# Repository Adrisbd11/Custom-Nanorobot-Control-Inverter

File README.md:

# Scalable Power Inverter for Precision Magnetic Field Control
This project is motivated by the growing interest in magnetic actuation systems for controlling microrobots and nanorobots in biomedical applications. These devices can be guided remotely using externally generated magnetic fields, enabling precise navigation inside the human body without the need for invasive procedures. Potential applications include targeted drug delivery, minimally invasive surgery, and the removal of blockages in blood vessels.

To achieve accurate control of these robots, it is necessary to generate well-defined and time-varying magnetic fields. This is typically done using current-driven coils, where the magnetic field is directly related to the current flowing through the windings. As a result, precise current control becomes a critical requirement for reliable and repeatable operation.

In this context, the project focuses on the design of a power inverter capable of driving a high-inductance coil with controlled current. The system is designed to operate with a coil of approximately 300 mH, supplying currents in the range of 20–30 A, and powered from a 560 V DC bus. These specifications impose significant challenges in terms of voltage handling, current regulation, and transient management in an inductive load.

This implementation represents a first functional prototype intended for laboratory validation. However, the design is conceived with scalability in mind, allowing extension toward significantly larger and more complex systems requiring higher power levels, multiple coils, and more advanced magnetic field control.  The system is designed to operate with a coil of approximately 100 mH, supplying currents in the range of 1–15 A, and powered from a 60-100 V DC bus.

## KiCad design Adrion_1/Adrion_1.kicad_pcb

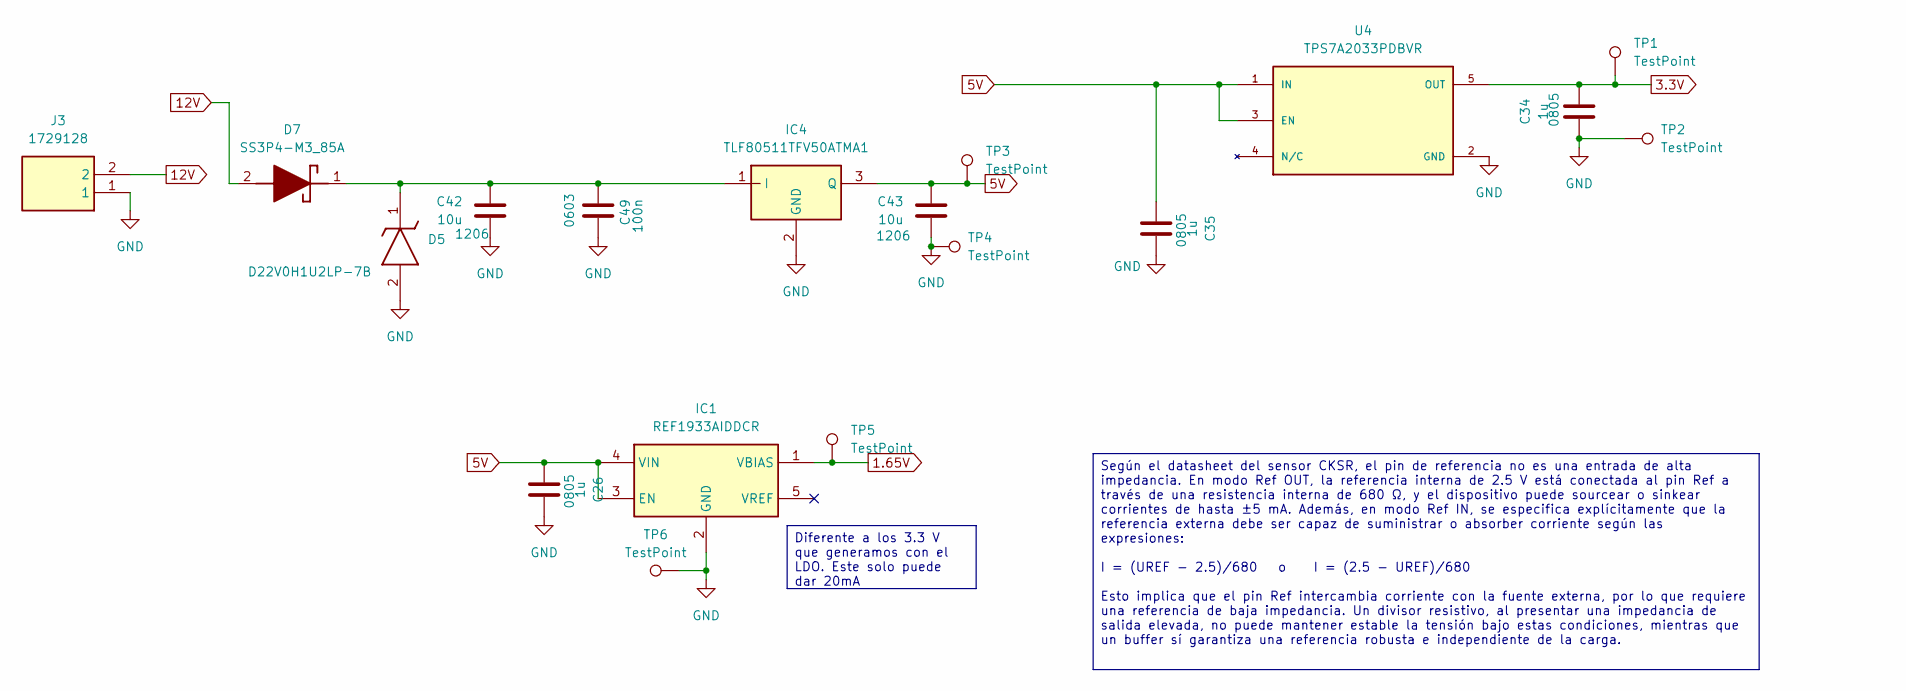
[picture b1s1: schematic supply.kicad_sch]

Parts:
C26, C34, C35: 1u; C_0805_2012Metric
C42, C43: 10u; C_1206_3216Metric
C49: 100n; C_0603_1608Metric
D5: D22V0H1U2LP-7B; D22V0H1U2LP7B; Manufacturer_Part_Number D22V0H1U2LP-7B
D7: SS3P4-M3_85A; SS3P4M385A; Manufacturer_Part_Number SS3P4-M3/85A; Mouser Part Number 625-SS3P4-M3/85A
IC1: REF1933AIDDCR; SOT95P280X110-5N; Manufacturer_Part_Number REF1933AIDDCR; Mouser Part Number 595-REF1933AIDDCR
IC4: TLF80511TFV50ATMA1; IDD09E60; Manufacturer_Part_Number TLF80511TFV50ATMA1; Mouser Part Number 726-TLF80511TFV50ATM
J3: 1729128; Manufacturer_Part_Number 1729128; Mouser Part Number 651-1729128
TP1, TP2, TP3, TP4, TP5, TP6: TestPoint; TestPoint_Pad_D1.0mm
U4: TPS7A2033PDBVR; SOT95P280X145-5N; PARTREV H

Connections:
1.65V: IC1.1 (VBIAS), TP5.1; also elsewhere on the board
3.3V: C34.2, TP1.1, U4.5 (OUT); also elsewhere on the board
5V: C26.1, C35.1, C43.1, IC1.3 (EN), IC1.4 (VIN), IC4.3 (Q), TP3.1, U4.1 (IN), U4.3 (EN); also elsewhere on the board
12V: D7.2 (A), J3.2; also elsewhere on the board
GND: C26.2, C34.1, C35.2, C42.2, C43.2, C49.1, D5.2 (A), IC1.2 (GND), IC4.2 (GND), J3.1, TP2.1, TP4.1, TP6.1, U4.2 (GND); also elsewhere on the board
unnamed: C42.1, C49.2, D5.1 (K), D7.1 (K), IC4.1 (I)

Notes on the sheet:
Diferente a los 3.3 V que generamos con el LDO. Este solo puede dar 20mA
Según el datasheet del sensor CKSR, el pin de referencia no es una entrada de alta impedancia. En modo Ref OUT, la referencia interna de 2.5 V está conectada al pin Ref a través de una resistencia interna de 680 Ω, y el dispositivo puede sourcear o sinkear corrientes de hasta ±5 mA. Además, en modo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

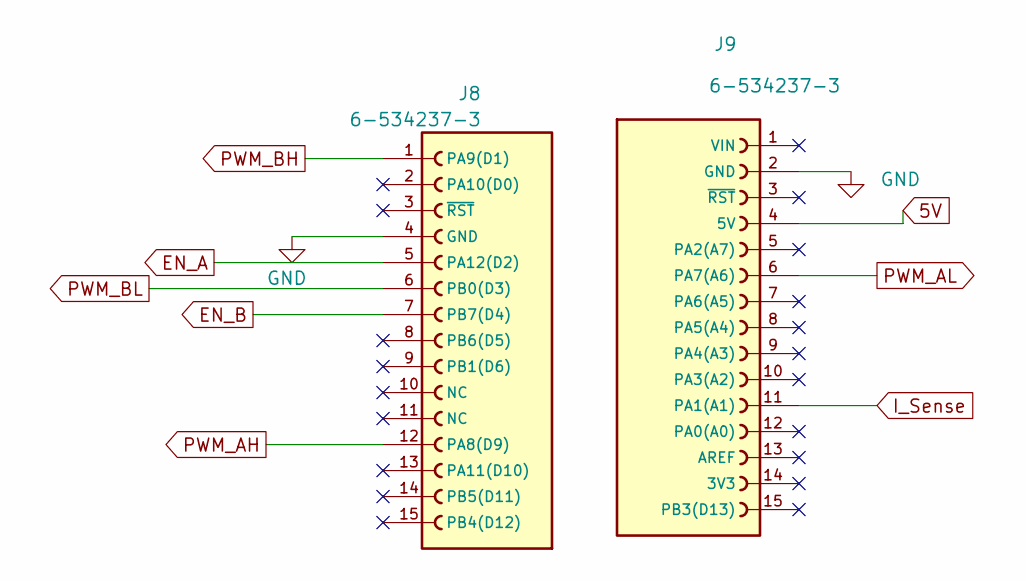
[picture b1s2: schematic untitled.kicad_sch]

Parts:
J8, J9: 6-534237-3; TE_6-534237-3; PARTREV R

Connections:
5V: J9.4 (5V); also elsewhere on the board
EN_A: J8.5 (PA12(D2)); also elsewhere on the board
EN_B: J8.7 (PB7(D4)); also elsewhere on the board
GND: J8.4 (GND), J9.2 (GND); also elsewhere on the board
I_Sense: J9.11 (PA1(A1)); also elsewhere on the board
PWM_AH: J8.12 (PA8(D9)); also elsewhere on the board
PWM_AL: J9.6 (PA7(A6)); also elsewhere on the board
PWM_BH: J8.1 (PA9(D1)); also elsewhere on the board
PWM_BL: J8.6 (PB0(D3)); also elsewhere on the board

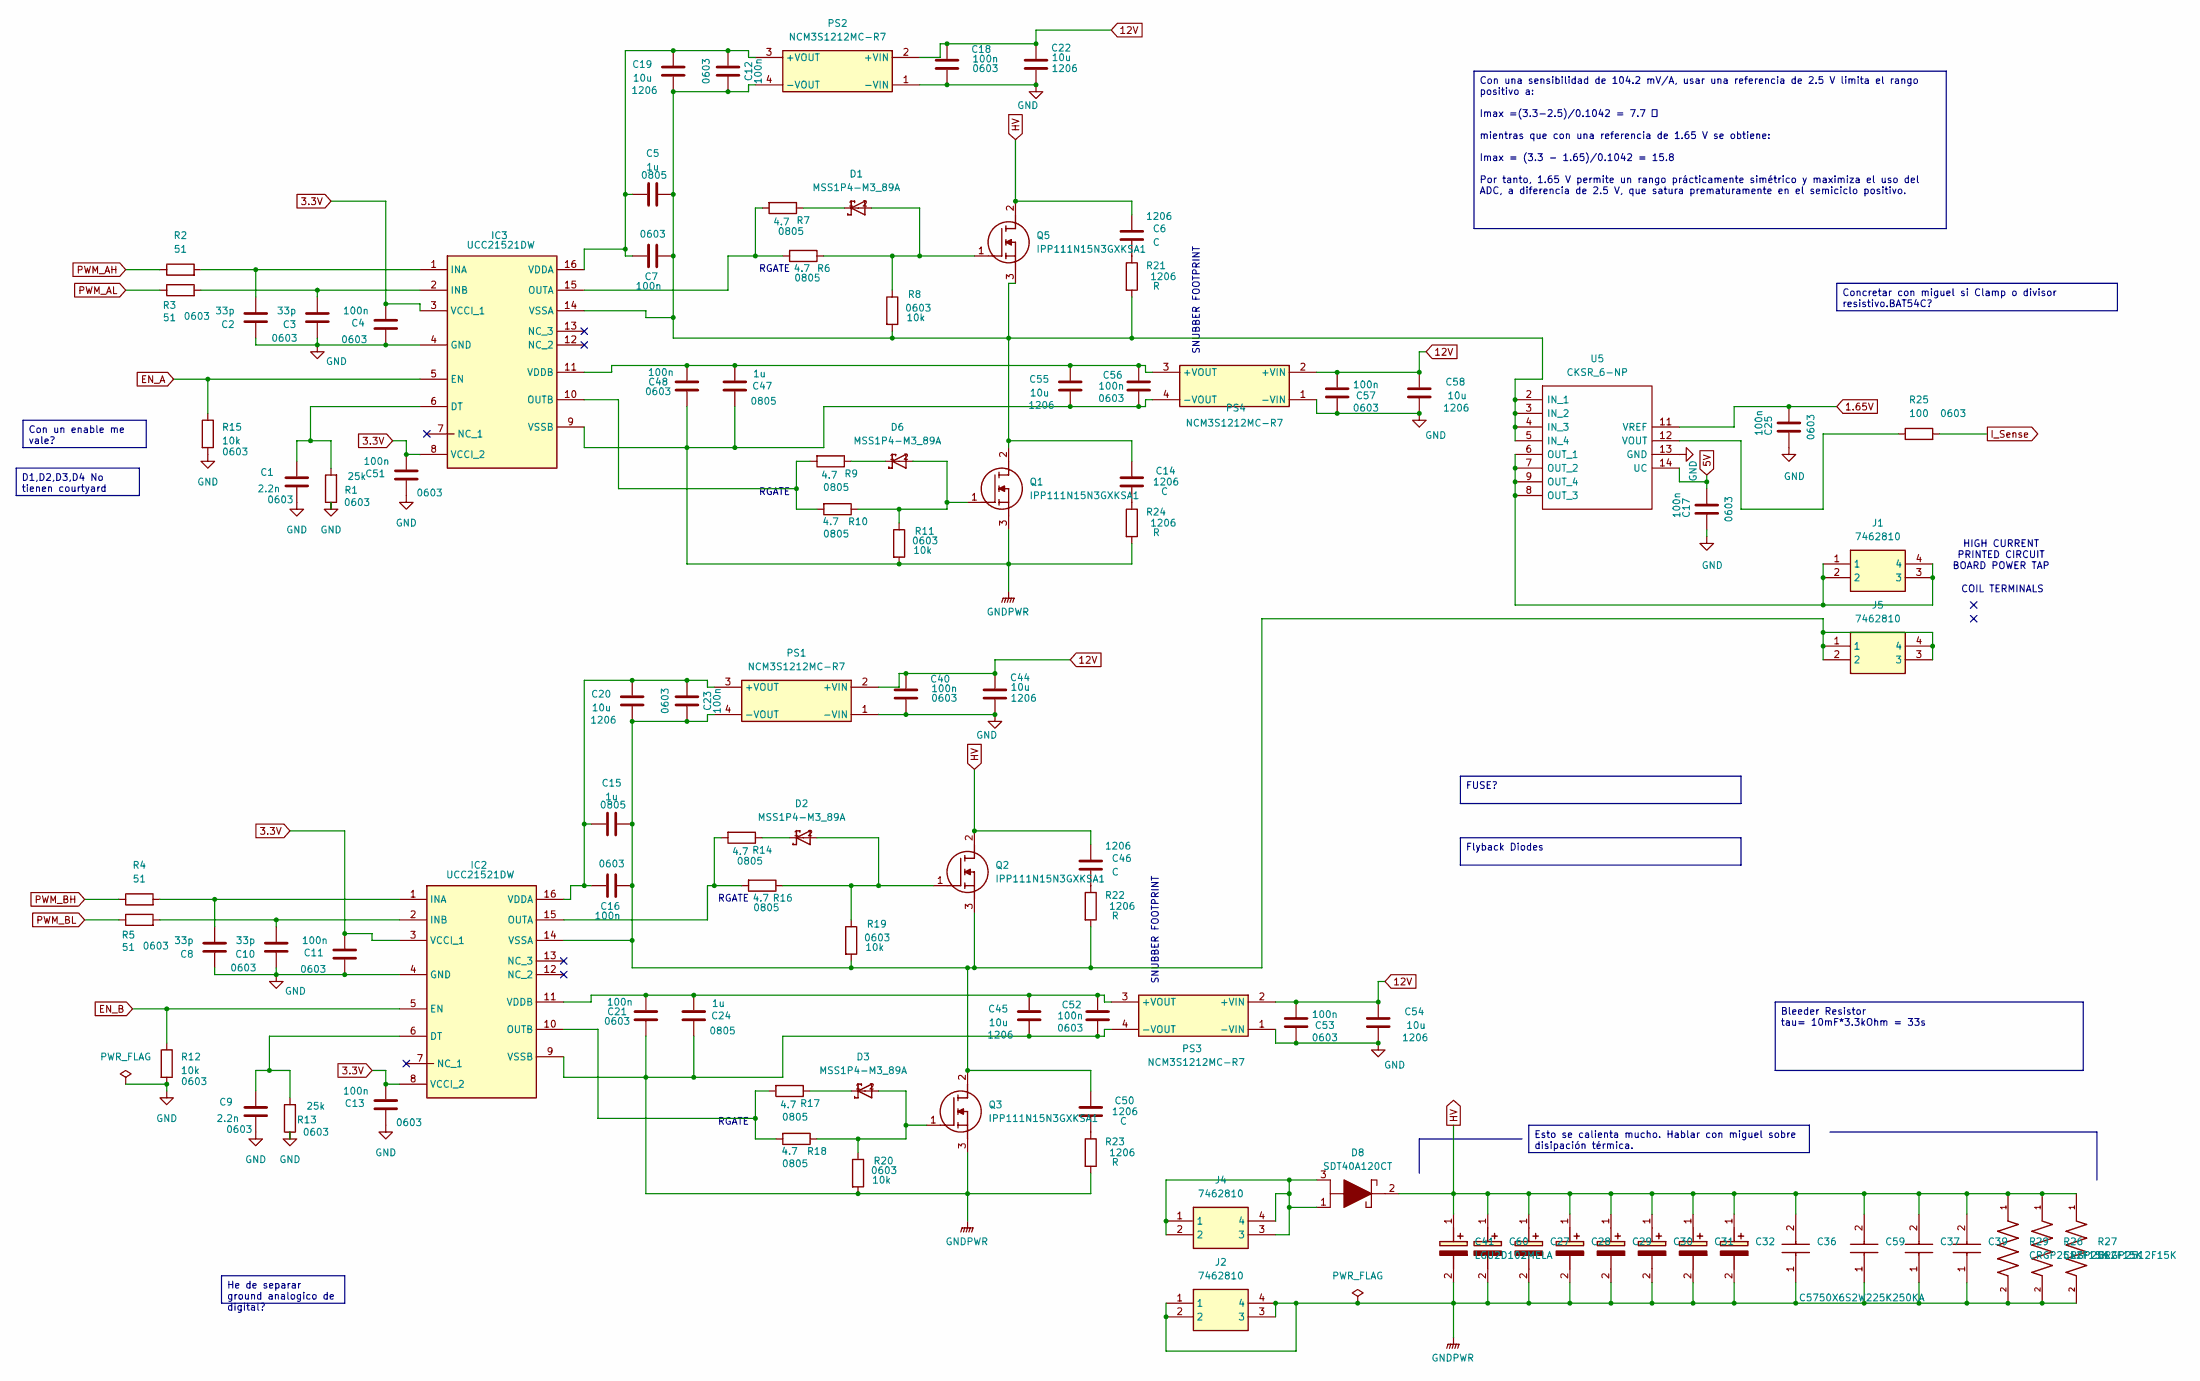
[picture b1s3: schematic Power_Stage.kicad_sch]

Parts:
C1, C9: 2.2n; C_0603_1608Metric_Pad1.08x0.95mm_HandSolder
C2, C3, C8, C10: 33p; C_0603_1608Metric_Pad1.08x0.95mm_HandSolder
C4, C11, C13, C51: 100n; C_0603_1608Metric_Pad1.08x0.95mm_HandSolder
C5, C15, C24, C47: 1u; C_0805_2012Metric
C6, C14, C46, C50: C; C_1206_3216Metric_Pad1.33x1.80mm_HandSolder
C7, C12, C16, C17, C18, C21, C23, C25, C40, C48, C52, C53, C56, C57: 100n; C_0603_1608Metric
C19, C20, C22, C44, C45, C54, C55, C58: 10u; C_1206_3216Metric
C27, C28, C29, C30, C31, C32, C41, C60: LGU2D102MELA; Manufacturer_Part_Number LGU2D102MELA; Mouser Part Number 647-LGU2D102MELA
C36, C37, C39, C59: C5750X6S2W225K250KA; C5750_Commercial; Manufacturer_Part_Number C5750X6S2W225K250KA; Mouser Part Number 810-C5750X6S2W225KKA
D1, D2, D3, D6: MSS1P4-M3_89A; DIODE_MSS1P4-M3_89A
D8: SDT40A120CT; TO254P1066X482X2286-3; Manufacturer_Part_Number STPS20200CTN
IC2, IC3: UCC21521DW; SOIC127P1030X265-16N; Manufacturer_Part_Number UCC21521DW; Mouser Part Number 595-UCC21521DW
J1, J2, J4, J5: 7462810; Manufacturer_Part_Number 7462810; Mouser Part Number 710-7462810
PS1, PS2, PS3, PS4: NCM3S1212MC-R7; NCM3S1212MCR7; Manufacturer_Part_Number NCM3S1212MC-R7
Q1, Q2, Q3, Q5: IPP111N15N3GXKSA1; TO254P457X1003X2115-3P; Manufacturer_Part_Number IPP111N15N3GXKSA1; Mouser Part Number 726-IPP111N15N3GXKSA
R1, R13: 25k; R_0603_1608Metric_Pad0.98x0.95mm_HandSolder
R2, R3, R4, R5: 51; R_0603_1608Metric_Pad0.98x0.95mm_HandSolder
R6, R7, R9, R10, R14, R16, R17, R18: 4.7; R_0805_2012Metric_Pad1.20x1.40mm_HandSolder
R8, R11, R12, R15, R19, R20: 10k; R_0603_1608Metric_Pad0.98x0.95mm_HandSolder
R21, R22, R23, R24: R; R_1206_3216Metric_Pad1.30x1.75mm_HandSolder
R25: 100; R_0603_1608Metric_Pad0.98x0.95mm_HandSolder
R26, R27, R29: CRGP2512F15K; RESC6332X65N
U5: CKSR_6-NP; CKSR6NP; Manufacturer_Part_Number CKSR 6-NP; Mouser Part Number 61-CKSR6-NP

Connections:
1.65V: C25.1, U5.11 (VREF); also elsewhere on the board
3.3V: C4.2, C11.2, C13.2, C51.2, IC2.3 (VCCI_1), IC2.8 (VCCI_2), IC3.3 (VCCI_1), IC3.8 (VCCI_2); also elsewhere on the board
5V: C17.1, U5.14 (UC); also elsewhere on the board
12V: C18.1, C22.1, C40.1, C44.1, C53.1, C54.1, C57.1, C58.1, PS1.2 (+VIN), PS2.2 (+VIN), PS3.2 (+VIN), PS4.2 (+VIN); also elsewhere on the board
EN_A: IC3.5 (EN), R15.1; also elsewhere on the board
EN_B: IC2.5 (EN), R12.1; also elsewhere on the board
GND: C1.2, C2.1, C3.1, C4.1, C8.1, C9.2, C10.1, C11.1, C13.1, C17.2, C18.2, C22.2, C25.2, C40.2, C44.2, C51.1, C53.2, C54.2, C57.2, C58.2, IC2.4 (GND), IC3.4 (GND), PS1.1 (-VIN), PS2.1 (-VIN), PS3.1 (-VIN), PS4.1 (-VIN), R1.1, R12.2, R13.1, R15.2, U5.13 (GND); also elsewhere on the board
GNDPWR: C21.2, C24.2, C27.2 (-), C28.2 (-), C29.2 (-), C30.2 (-), C31.2 (-), C32.2 (-), C36.1, C37.1, C39.1, C41.2 (-), C45.2, C47.2, C48.2, C52.2, C55.2, C56.2, C59.1, C60.2 (-), IC2.9 (VSSB), IC3.9 (VSSB), J2.1, J2.2, J2.3, J2.4, PS3.4 (-VOUT), PS4.4 (-VOUT), Q1.3 (S), Q3.3 (S), R11.2, R20.2, R23.2, R24.2, R26.2, R27.2, R29.2
HV: C6.1, C27.1 (+), C28.1 (+), C29.1 (+), C30.1 (+), C31.1 (+), C32.1 (+), C36.2, C37.2, C39.2, C41.1 (+), C46.1, C59.2, C60.1 (+), D8.2, Q2.2 (D), Q5.2 (D), R26.1, R27.1, R29.1
I_Sense: R25.2; also elsewhere on the board
unnamed: C6.2, R21.1
unnamed: C14.2, R24.1
unnamed: C46.2, R22.1
unnamed: C50.2, R23.1
unnamed: D1.1, R7.1
unnamed: D2.1, R14.1
unnamed: D3.1, R17.1
unnamed: D6.1, R9.1
unnamed: D8.1, D8.3, J4.1, J4.2, J4.3, J4.4
unnamed: C9.1, IC2.6 (DT), R13.2
unnamed: C8.2, IC2.1 (INA), R4.2
unnamed: C10.2, IC2.2 (INB), R5.2
unnamed: IC2.15 (OUTA), R14.2, R16.2
unnamed: IC2.10 (OUTB), R17.2, R18.2
unnamed: C15.1, C16.1, C20.1, C23.2, IC2.16 (VDDA), PS1.3 (+VOUT)
unnamed: C21.1, C24.1, C45.1, C52.1, IC2.11 (VDDB), PS3.3 (+VOUT)
unnamed: C15.2, C16.2, C20.2, C23.1, C50.1, IC2.14 (VSSA), J5.1, J5.2, J5.3, J5.4, PS1.4 (-VOUT), Q2.3 (S), Q3.2 (D), R19.2, R22.2
unnamed: C1.1, IC3.6 (DT), R1.2
unnamed: C2.2, IC3.1 (INA), R2.2
unnamed: C3.2, IC3.2 (INB), R3.2
unnamed: IC3.15 (OUTA), R6.2, R7.2
unnamed: IC3.10 (OUTB), R9.2, R10.2
unnamed: C5.1, C7.1, C12.2, C19.1, IC3.16 (VDDA), PS2.3 (+VOUT)
unnamed: C47.1, C48.1, C55.1, C56.1, IC3.11 (VDDB), PS4.3 (+VOUT)
unnamed: C5.2, C7.2, C12.1, C14.1, C19.2, IC3.14 (VSSA), PS2.4 (-VOUT), Q1.2 (D), Q5.3 (S), R8.2, R21.2, U5.2 (IN_1), U5.3 (IN_2), U5.4 (IN_3), U5.5 (IN_4)
unnamed: D6.2, Q1.1 (G), R10.1, R11.1
unnamed: D2.2, Q2.1 (G), R16.1, R19.1
unnamed: D3.2, Q3.1 (G), R18.1, R20.1
unnamed: D1.2, Q5.1 (G), R6.1, R8.1
unnamed: J1.1, J1.2, J1.3, J1.4, U5.6 (OUT_1), U5.7 (OUT_2), U5.8 (OUT_3), U5.9 (OUT_4)
unnamed: R25.1, U5.12 (VOUT)
PWM_AH: R2.1; also elsewhere on the board
PWM_AL: R3.1; also elsewhere on the board
PWM_BH: R4.1; also elsewhere on the board
PWM_BL: R5.1; also elsewhere on the board

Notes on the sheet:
RGATE
RGATE
COIL TERMINALS
SNUBBER FOOTPRINT
HIGH CURRENT PRINTED CIRCUIT BOARD POWER TAP
Con un enable me vale?
FUSE?
Bleeder Resistor tau= 10mF*3.3kOhm = 33s
He de separar ground analogico de digital?
Esto se calienta mucho. Hablar con miguel sobre disipación térmica.
D1,D2,D3,D4 No tienen courtyard
Flyback Diodes
Con una sensibilidad de 104.2 mV/A, usar una referencia de 2.5 V limita el rango positivo a: Imax =(3.3−2.5)/0.1042 = 7.7 𝐴 mientras que con una referencia de 1.65 V se obtiene: Imax = (3.3 − 1.65)/0.1042 = 15.8 Por tanto, 1.65 V permite un rango prácticamente simétrico y maximiza el uso del ADC, a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
Concretar con miguel si Clamp o divisor resistivo.BAT54C?

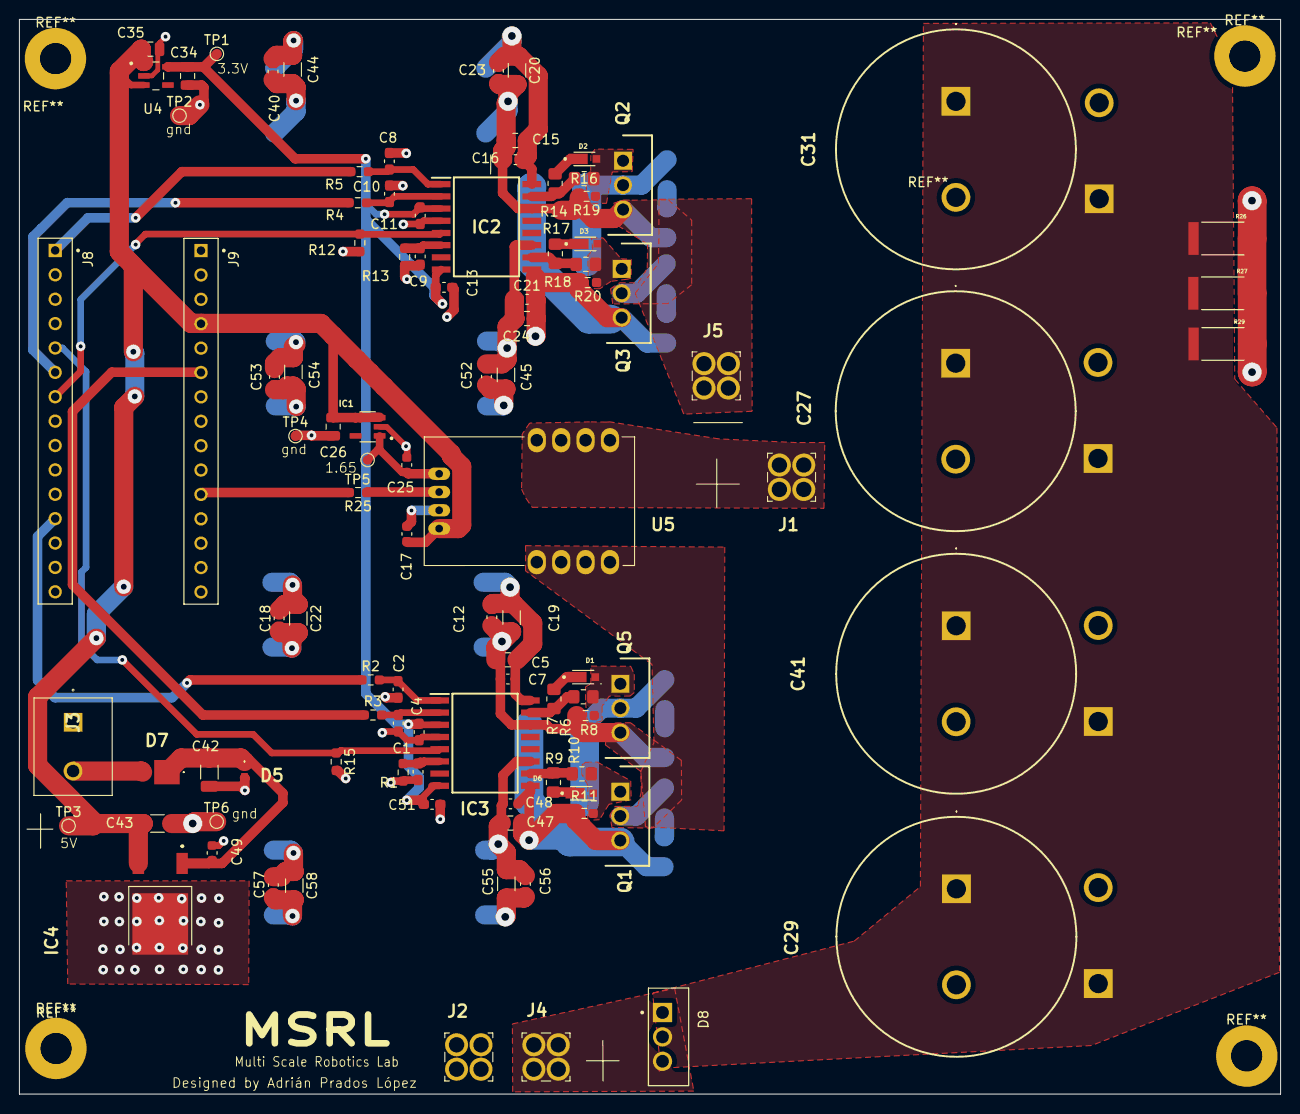
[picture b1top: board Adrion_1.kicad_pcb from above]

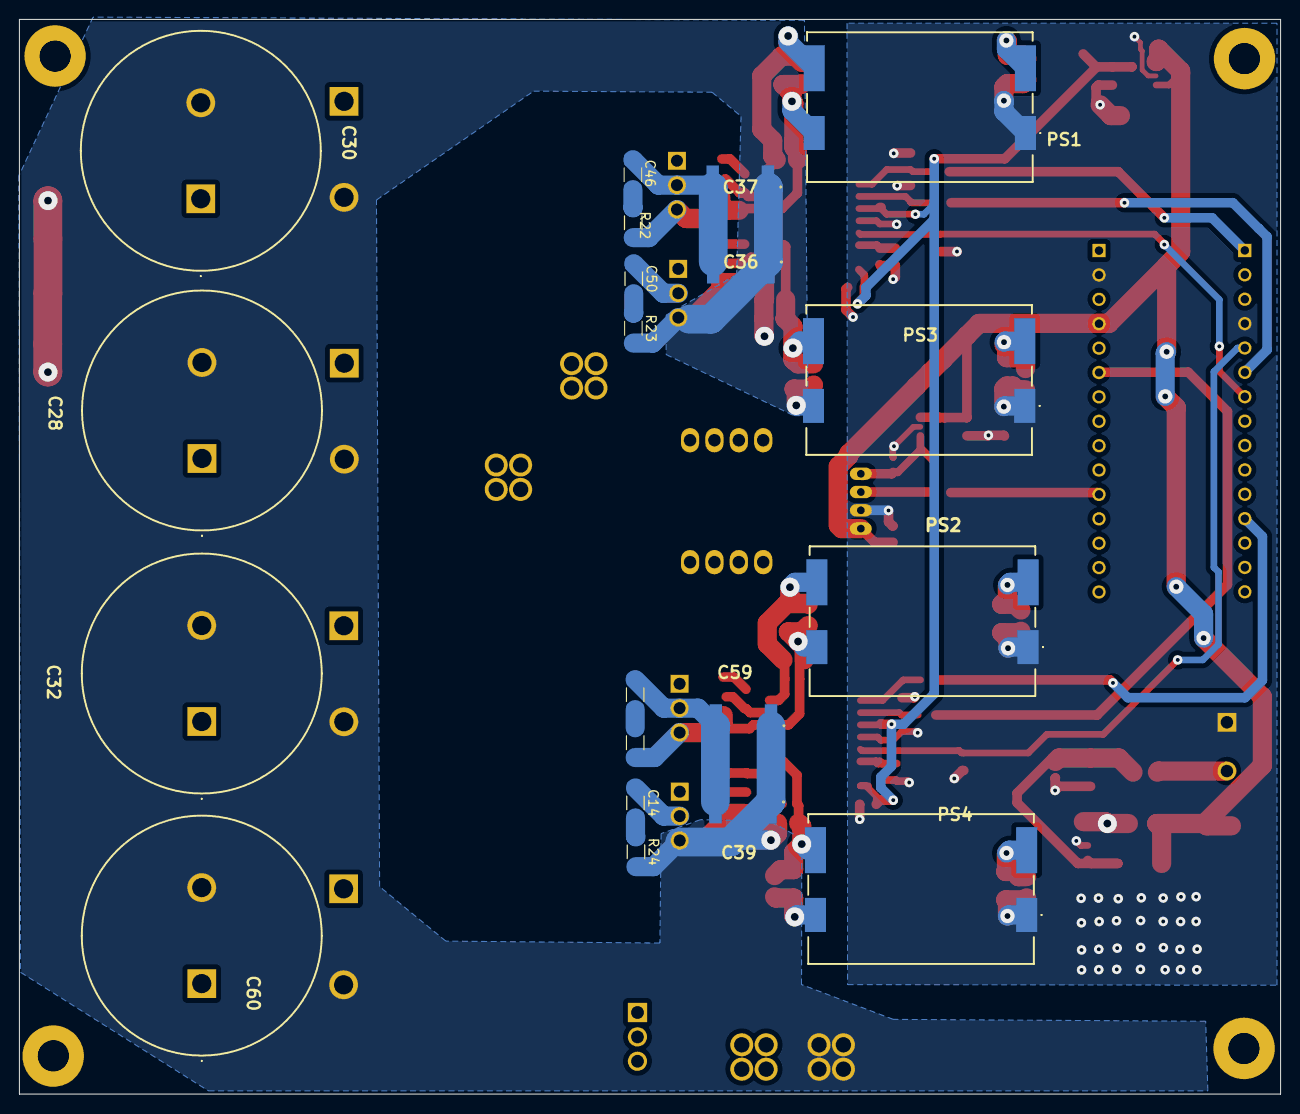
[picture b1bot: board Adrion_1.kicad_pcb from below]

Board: 4 copper layers, 131.4 x 111.9 mm, 120 parts (20 on the bottom side), 46 nets.

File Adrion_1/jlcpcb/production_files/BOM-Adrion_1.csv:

Comment,Designator,Footprint,LCSC,Quantity
100,R25,R_0603_1608Metric_Pad0.98x0.95mm_HandSolder,C22775,1
100n,"C12,C16,C18,C21,C23,C40,C48,C52,C53,C56,C57,C7",C_0603_1608Metric,C125205,12
100n,"C11,C13,C17,C25,C4,C49,C51",C_0603_1608Metric_Pad1.08x0.95mm_HandSolder,C1590,7
10k,"R11,R12,R15,R19,R20,R8",R_0603_1608Metric_Pad0.98x0.95mm_HandSolder,C25804,6
10u,"C19,C20,C22,C42,C43,C44,C45,C54,C55",C_1206_3216Metric,C13585,9
1729128,J3,1729128,C7509570,1
1u,"C15,C47,C5",C_0805_2012Metric,C141772,3
1u,"C26,C34,C35",C_0805_2012Metric,C1712,3
1u,C24,C_0805_2012Metric,C76645,1
2.2n,"C1,C9",C_0603_1608Metric_Pad1.08x0.95mm_HandSolder,C1604,2
25k,"R1,R13",R_0603_1608Metric_Pad0.98x0.95mm_HandSolder,C2828637,2
33p,C8,C_0603_1608Metric_Pad1.08x0.95mm_HandSolder,C1026,1
33p,"C10,C2,C3",C_0603_1608Metric_Pad1.08x0.95mm_HandSolder,C1663,3
4.7,"R10,R14,R16,R17,R18,R6,R7,R9",R_0805_2012Metric_Pad1.20x1.40mm_HandSolder,C17675,8
51,"R2,R3,R4,R5",R_0603_1608Metric_Pad0.98x0.95mm_HandSolder,C23197,4
7462810,"J1,J2,J4,J5",7462810,C5542679,4
CKSR_6-NP,U5,CKSR6NP,C454684,1
CRGP2512F15K,"R26,R27,R29",RESC6332X65N,C4001351,3
D22V0H1U2LP-7B,D5,D22V0H1U2LP7B,C7156668,1
IPP111N15N3GXKSA1,"Q1,Q2,Q3,Q5",TO254P457X1003X2115-3P,C513207,4
LGU2D102MELA,"C27,C28,C29,C30,C31,C32",LGU2D102MELA,C5781838,6
MSS1P4-M3_89A,"D1,D2,D3,D6",DIODE_MSS1P4-M3_89A,C2980309,4
REF1933AIDDCR,IC1,SOT95P280X110-5N,C2157197,1
TPS7A2033PDBVR,U4,SOT95P280X145-5N,C2862740,1
UCC21521DW,"IC2,IC3",SOIC127P1030X265-16N,C2861324,2
R,R24,R_1206_3216Metric_Pad1.30x1.75mm_HandSolder,,1
R,R23,R_1206_3216Metric_Pad1.30x1.75mm_HandSolder,,1
R,R22,R_1206_3216Metric_Pad1.30x1.75mm_HandSolder,,1
R,R21,R_1206_3216Metric_Pad1.30x1.75mm_HandSolder,,1
NCM3S1212MC-R7,PS4,NCM3S1212MCR7,,1
NCM3S1212MC-R7,PS3,NCM3S1212MCR7,,1
NCM3S1212MC-R7,PS2,NCM3S1212MCR7,,1
NCM3S1212MC-R7,PS1,NCM3S1212MCR7,,1
SDT40A120CT,D8,TO254P1066X482X2286-3,,1
SS3P4-M3_85A,D7,SS3P4M385A,,1
10u,C58,C_1206_3216Metric,,1
C,C50,C_1206_3216Metric_Pad1.33x1.80mm_HandSolder,,1
C,C46,C_1206_3216Metric_Pad1.33x1.80mm_HandSolder,,1
C5750X6S2W225K250KA,C39,C5750_Commercial,,1
C5750X6S2W225K250KA,C37,C5750_Commercial,,1
C5750X6S2W225K250KA,C36,C5750_Commercial,,1
C,C14,C_1206_3216Metric_Pad1.33x1.80mm_HandSolder,,1
C,C6,C_1206_3216Metric_Pad1.33x1.80mm_HandSolder,,1
C5750X6S2W225K250KA,C59,C5750_Commercial,,1
TLF80511TFV50ATMA1,IC4,IDD09E60,,1
LGU2D102MELA,C41,LGU2D102MELA,,1
LGU2D102MELA,C60,LGU2D102MELA,,1
6-534237-3,J9,TE_6-534237-3,,1
6-534237-3,J8,TE_6-534237-3,,1
TestPoint,TP4,TestPoint_Pad_D1.0mm,,1
TestPoint,TP6,TestPoint_Pad_D1.0mm,,1
TestPoint,TP5,TestPoint_Pad_D1.0mm,,1
TestPoint,TP3,TestPoint_Pad_D1.0mm,,1
TestPoint,TP2,TestPoint_Pad_D1.0mm,,1
TestPoint,TP1,TestPoint_Pad_D1.0mm,,1

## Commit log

2026-03-27 Add Adrion_1 KiCad project and backups
    Add new KiCad project "Adrion_1": initial PCB file (Adrion_1.kicad_pcb), project settings (.kicad_prl, .kicad_pro) and schematics (Adrion_1.kicad_sch, Adrion_1.kicad_sch-bak, Power_Stage.kicad_sch, s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
2026-04-10 Modificaciones
2026-04-14 Desarrollo
2026-04-14 Correcciones
2026-04-15 Correcion railes de tension papa
2026-04-17 Footprints
2026-04-17 Datasheets
2026-04-20 meduelelacabeza
2026-04-28 Mamita he empezado el layout. Vaya show
2026-04-28 Layout
2026-04-30 Routing, Placement, Datasheets actualizado
2026-04-30 arrreglos, venitilador y disipadores primera version
2026-05-08 FirstPrototype
    First Prototype sent
